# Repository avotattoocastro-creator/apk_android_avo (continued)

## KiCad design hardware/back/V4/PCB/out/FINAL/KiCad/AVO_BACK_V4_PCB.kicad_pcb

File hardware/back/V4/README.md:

# AVO BACK V4 · espalda compacta (PCB propia + URTK1.2 + carcasa más corta)

Rediseño conjunto de la electrónica y la carcasa de la espalda de AVO Performance Horse.
**Estado: DISEÑADO Y COMPROBADO POR SOFTWARE · NO FABRICADO · NO VERIFICADO EN HARDWARE.**

**REV B (30/10/2026): sin Qi ni sensor Hall.** Alimentación por **3 contactos en el fondo** (tornillos M2 avellanados con
junta tórica): **SYS** y **BAT** en la cola, donde estaba el reed, y **GND** aparte.
- **Soporte del chaleco:** 2 pines con muelle unidos por un hilo puentean SYS–BAT. Al poner la cápsula se enciende; al
  quitarla queda a 0 V.
- **Base de carga:** cargador Li-ion externo entre BAT y GND, con la electrónica apagada.
- **USB-C:** se mantiene para el taller (datos y carga).
- **REV A** (con Qi y Hall, puerta superada) congelada en `PCB_REV_A_QI/`.
- **Probarlo antes en la espalda actual** (Rev E + Heltec): `DOCS/PROTOTIPO_POGO_REV_E.md` y `PROTOTIPO_POGO_REV_E6/`.

## Resultado
| Parámetro | Espalda actual (Rev E.5 + Heltec) | Nueva V4 | Diferencia |
|---|---|---|---|
| Longitud de la cápsula | 166,2 mm | **118,2 mm** | **−48,0 mm (−28,9 %)** |
| Anchura | 59,0 mm | 59,0 mm | 0 |
| Grosor de la cápsula | 17,1 mm | **17,1 mm** | **0** (no aumenta) |
| Grosor del conjunto (cápsula + soporte + tela + contraplaca) | 28,2 mm | 28,2 mm | 0 |
| Volumen exterior de la cápsula | 157,8 cm³ | 110,1 cm³ | −47,7 cm³ (−30,3 %) |
| Peso de las piezas impresas (macizas, PETG/TPU) | 208 g | ≈ 131 g | **≈ −77 g (−37 %)** |
| Peso de la electrónica | Heltec + Pololu + módulo Qi + cables | PCB V4 ≈ 9 g (estimado) | similar (sin medir) |
| Autonomía (2000 mAh) | ~8 h (estimada, 190–230 mA) | **≈ 7,8 h** (estimada, ≈ 230 mA) | ≥ 4 h exigidas |
| Consumo fuera del soporte | ZED sin cortar en algunas versiones (~70 mA) | **0 µA** (REV B: sin puente SYS–BAT la placa no tiene alimentación; solo el PCM de la celda) | |
| Placas | 3 (Heltec, URTK1.2, módulo Qi) + regulador Pololu | **2** (PCB V4 + URTK1.2) | −1 (−2 con el Pololu) |
| Cables entre placas | ZED (5–7 hilos), Qi, reed, batería, regulador | **1 mazo de 8 hilos** (URTK1.2 ↔ J4) + batería | |
| Carga | Qi (base inalámbrica) | **contactos BAT–GND** en la base de carga (REV B) · USB-C en el taller | |
| microSD | no | **sí** (SDMMC 4 bits) | |

**PCB REV B:** ruteada al 100 %; KiCad 9 en el CI (run 41048486880, `c1e0e26`; repetida en 41050496945, `6e5b54d`, con las existencias del TVS): DRC 0, ERC 0, 0 conexiones incompletas,
puerta de fabricación superada → `PCB/out/FINAL/` (61 piezas montadas). Su STEP, montado en el CAD a Z 2,5, no interfiere
con ninguna pieza ni con los tornillos de contacto (`CAD/VALIDACION/verificacion_pcb_step_v4.json`).
**PCB REV A** (congelada): puerta superada en el CI (run 40971520610, `3f81b45`) → `PCB_REV_A_QI/out/FINAL/`.

Cotas y volúmenes medidos sobre el modelo B-Rep (no sobre fotos). Pesos: volumen × densidad (PETG 1,27, TPU 1,20 g/cm³),
como en la Rev E.

## Cómo se consigue (sin aumentar el grosor)
- **La URTK1.2 va encima de la batería**, donde estaba la Heltec, a la misma altura (Z 9,6). La L, la torre y la antena
  no cambian de cota.
- **La PCB va en la cola**, el tramo que la antena Q39 obliga a tener por detrás del eje de la L y que en la Rev E
  estaba casi vacío. Bolsillo en la base a Z 2,5 (REV A: bobina Qi debajo; REV B: suelo macizo con los contactos).
- **Un solo ESP32-S3** (no dos): misma funcionalidad, menos consumo y menos superficie (`DOCS/ARQUITECTURA_Y_CONSUMO.md`).
- **Sin sensor de soporte (REV B)**: el propio soporte cierra el circuito (puente SYS–BAT); REV A usaba un Hall soldado.
- **Regulador propio del ZED con EN**: corta físicamente receptor y antena, sin el reinicio de la BACK 3.10.4.

Estudio completo de las alternativas A–D: `DOCS/ESTUDIO_DISTRIBUCION.md`.

## Carpetas
| Carpeta | Contenido |
|---|---|
| `CAD/fuente/` | modelo paramétrico FreeCAD 1.0.2 (`avo_back_v4_freecad.py`), verificación, exportación, voladizos, renders, plano |
| `CAD/STL/` | piezas orientadas para imprimir **sin soportes** + `posicion_montaje/` + probetas |
| `CAD/STEP/` | sólidos B-Rep por pieza, conjunto montado y explosionado |
| `CAD/IMAGENES/`, `CAD/PLANOS/` | vistas, vista explosionada, plano de dimensiones (PDF) y comparativa con la Rev E.5 |
| `CAD/VALIDACION/` | interferencias, STEP/STL, voladizos, informe del modelo |
| `PCB/fuente/` | generador del proyecto KiCad REV B (piezas, redes, colocación), reparación de ruteado, puerta de fabricación |
| `PCB_REV_A_QI/` | placa REV A con Qi y Hall (congelada, puerta superada) |
| `PROTOTIPO_POGO_REV_E6/` | base, soporte y base de carga Rev E.6 para probar los contactos en la espalda actual (Heltec) |
| `PCB/kicad/` | proyecto KiCad 9 editable |
| `PCB/out/` | ERC/DRC, esquema PDF, renders y — si la puerta pasa — `FINAL/` (Gerber, taladros, BOM y CPL de JLCPCB, STEP) |
| `../../../firmware/back/V4_0_0/` | firmware 4.0.0-dev2 de la placa V4 REV B (`../V3_8_0`: BACK 3.12.0 para el prototipo Heltec) |
| `DOCS/` | arquitectura y consumo, integración GNSS, distribución, montaje y riesgos |

## Ejes y origen (CAD, PCB y STEP)
X 0 = cara del cuello, X+ hacia la cola · Y 0 = eje de la L · Z 0 = cara inferior de la cápsula. La PCB de KiCad está en
las mismas coordenadas (x = X, y = 100 − Y; el STEP se exporta con origen de usuario 0 × 100 mm).

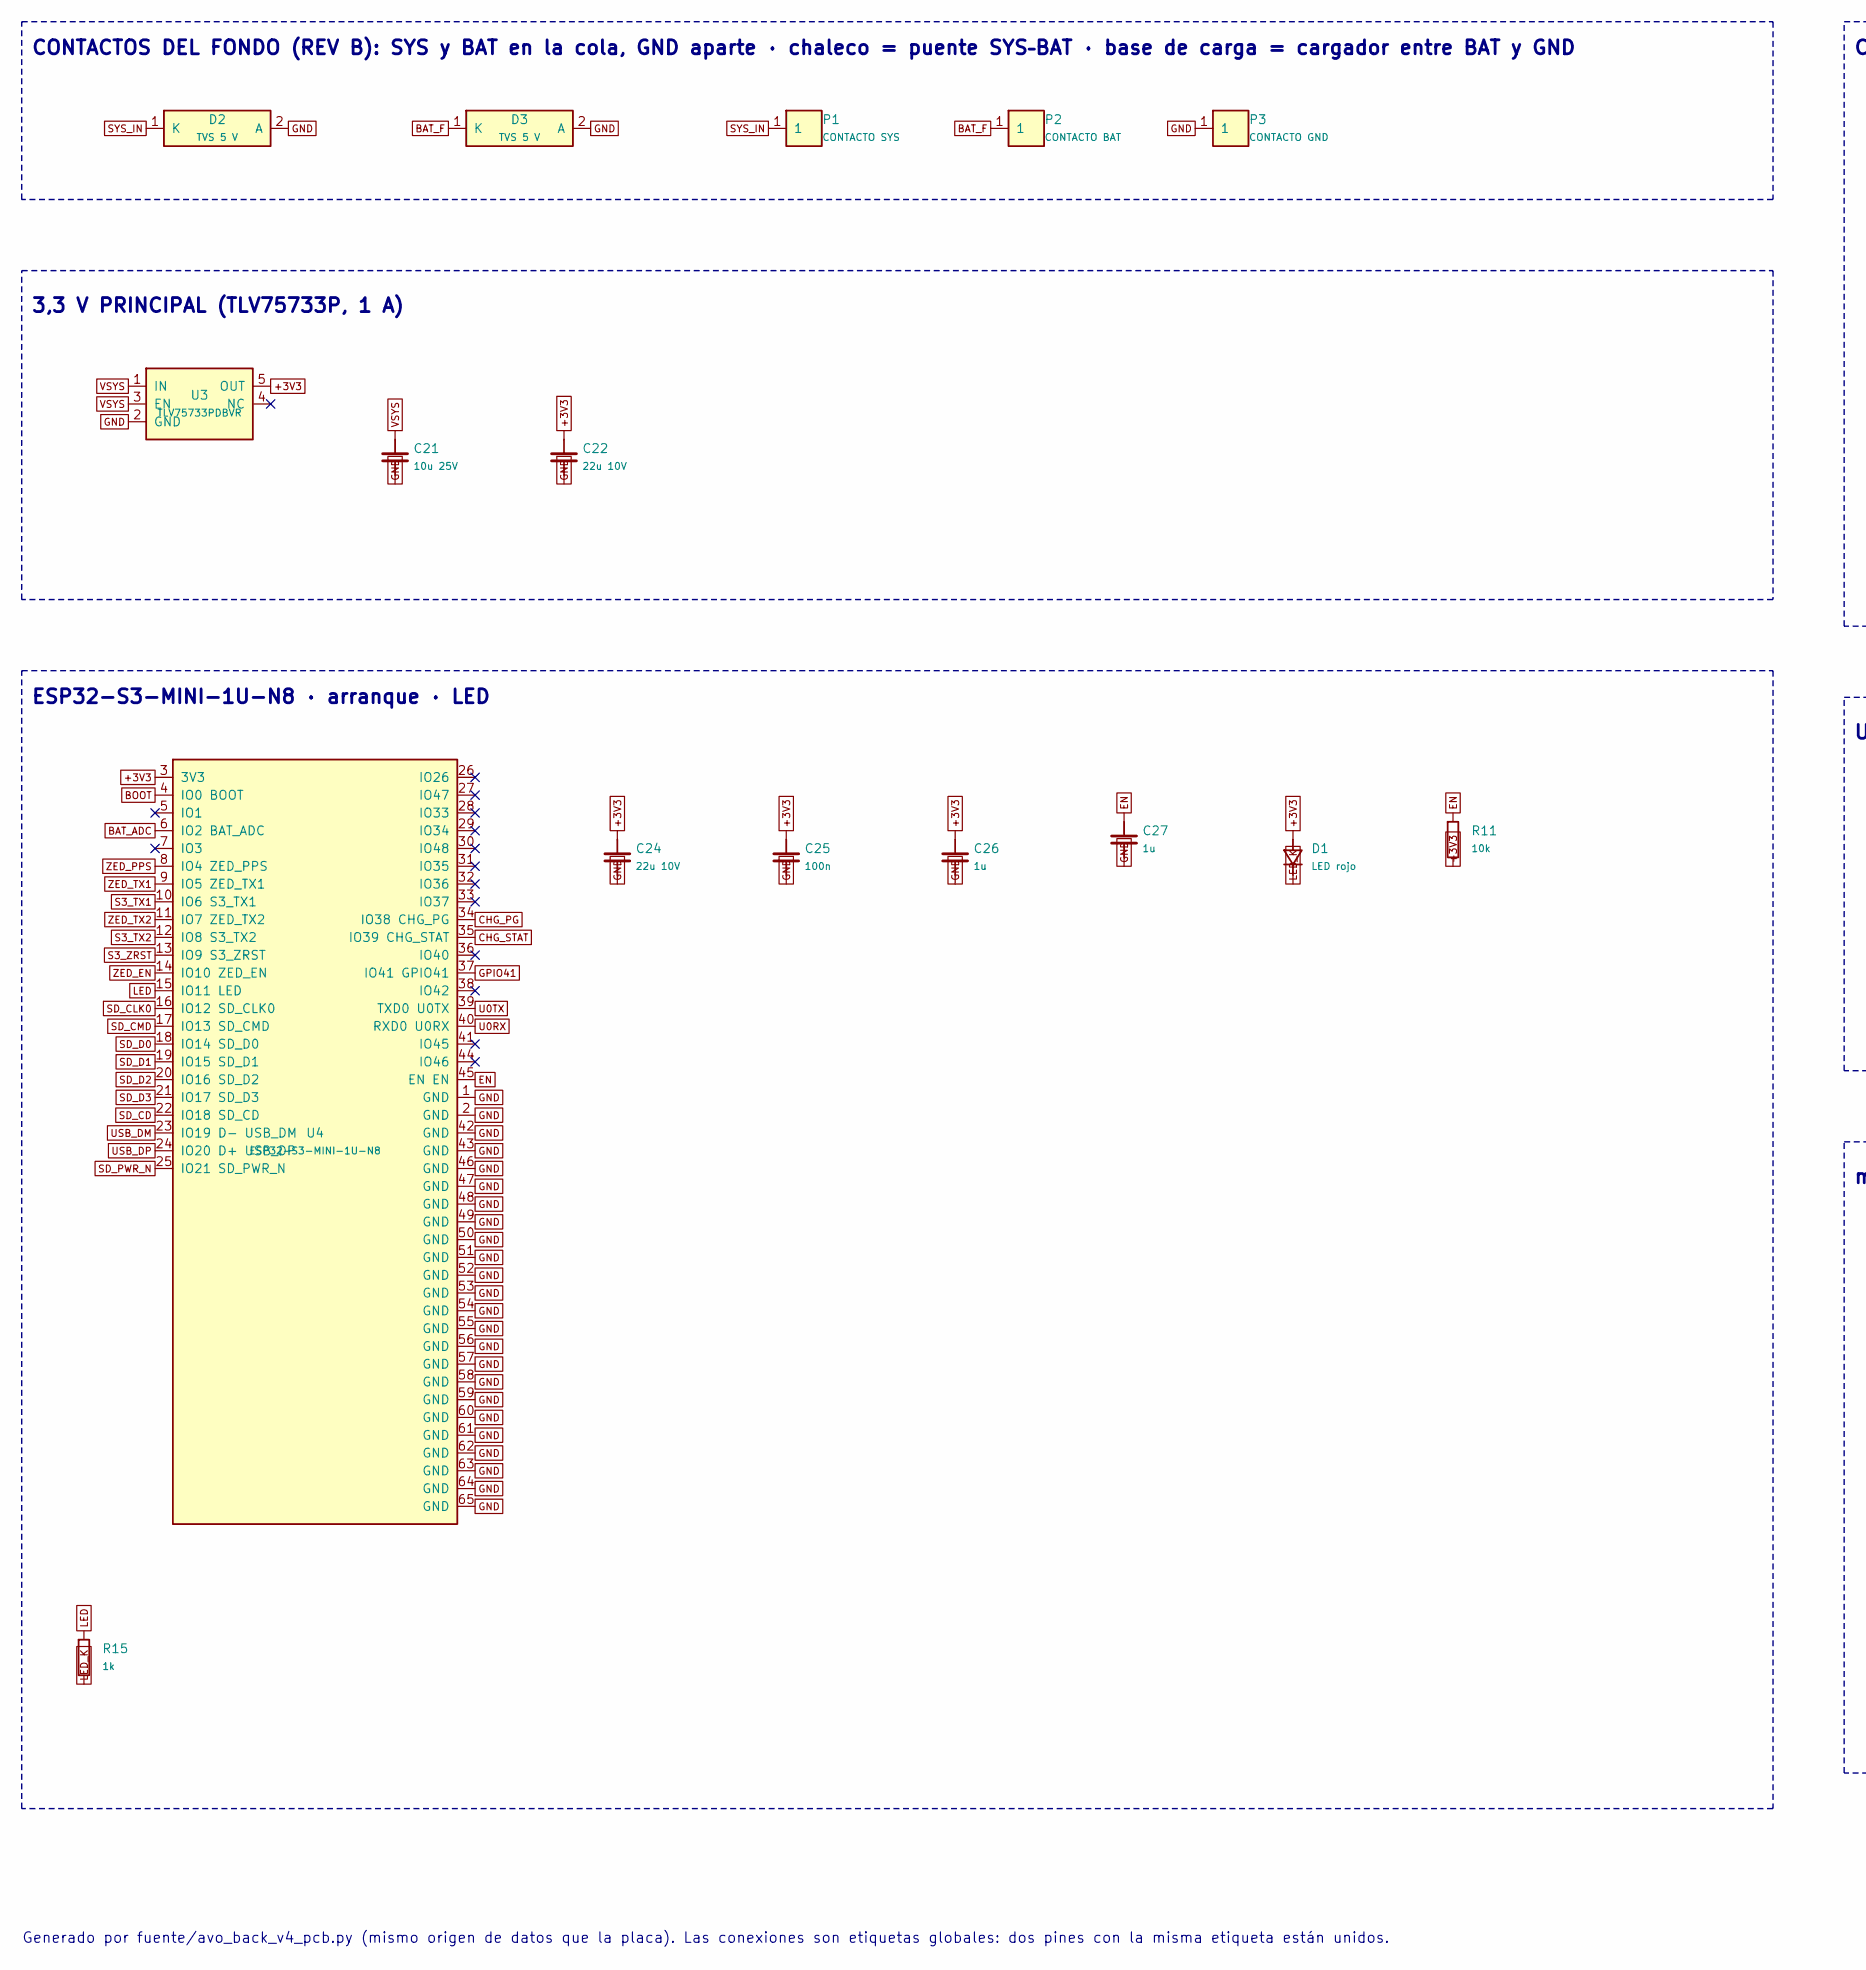
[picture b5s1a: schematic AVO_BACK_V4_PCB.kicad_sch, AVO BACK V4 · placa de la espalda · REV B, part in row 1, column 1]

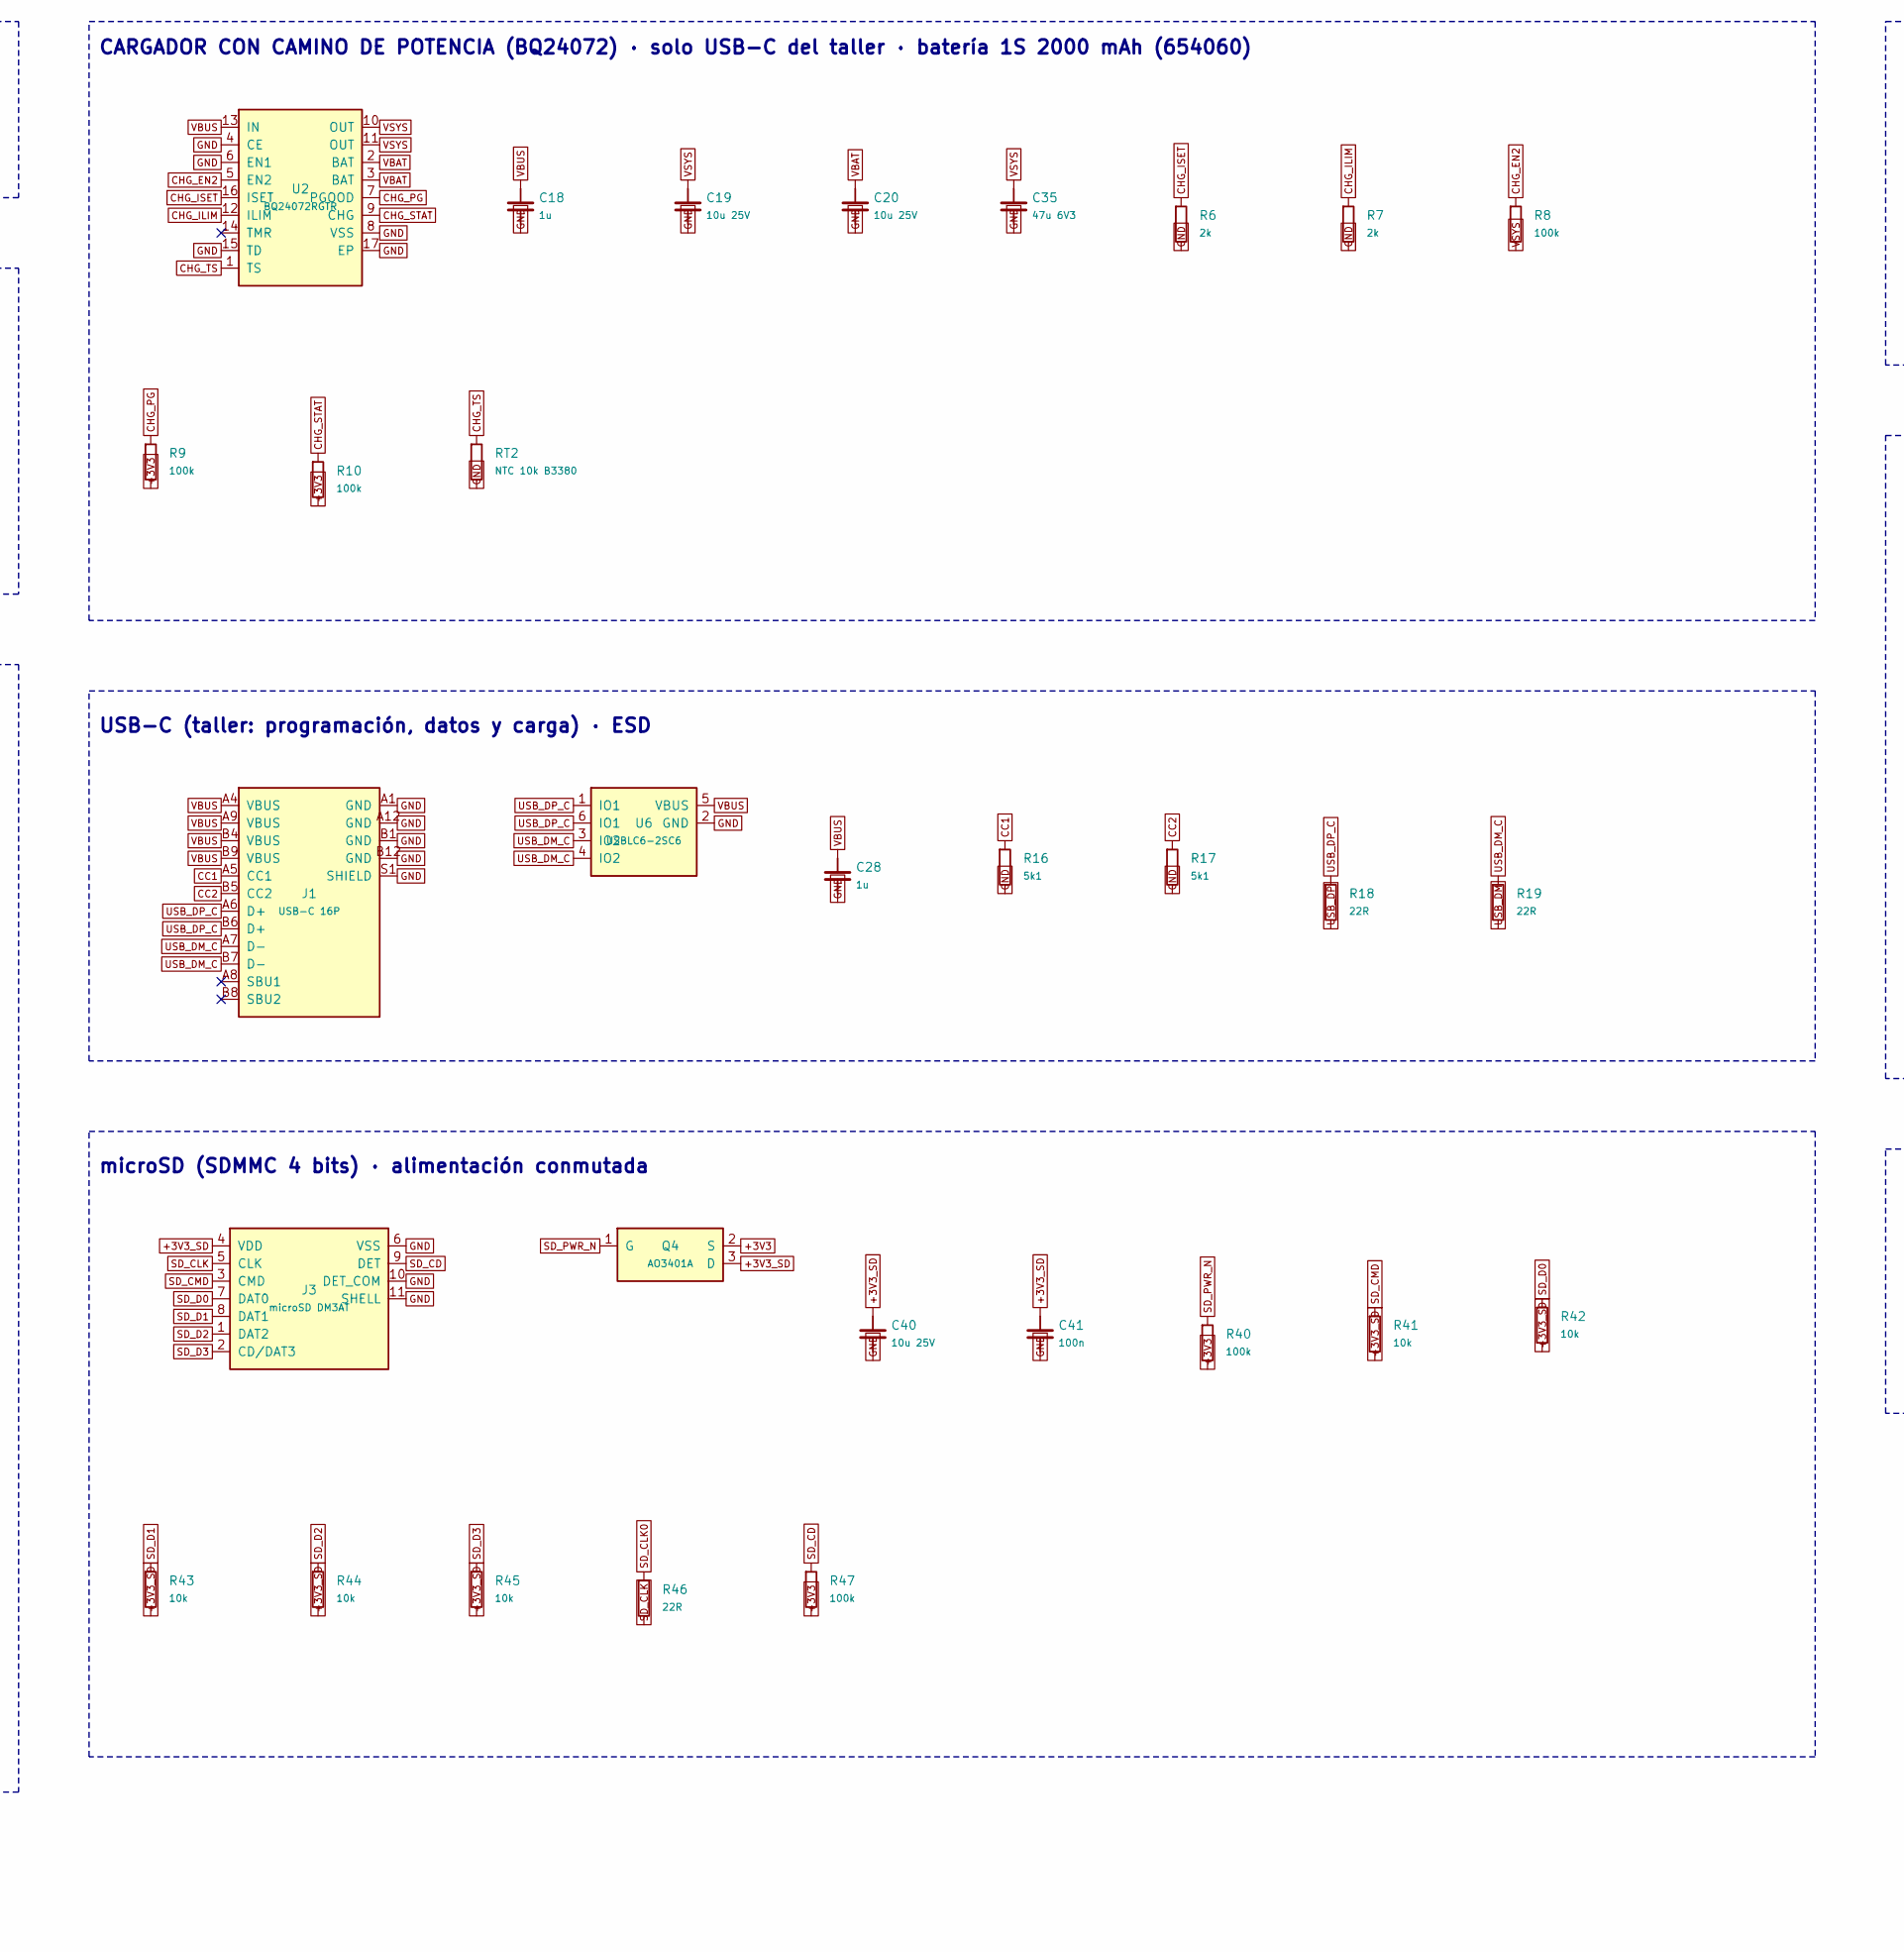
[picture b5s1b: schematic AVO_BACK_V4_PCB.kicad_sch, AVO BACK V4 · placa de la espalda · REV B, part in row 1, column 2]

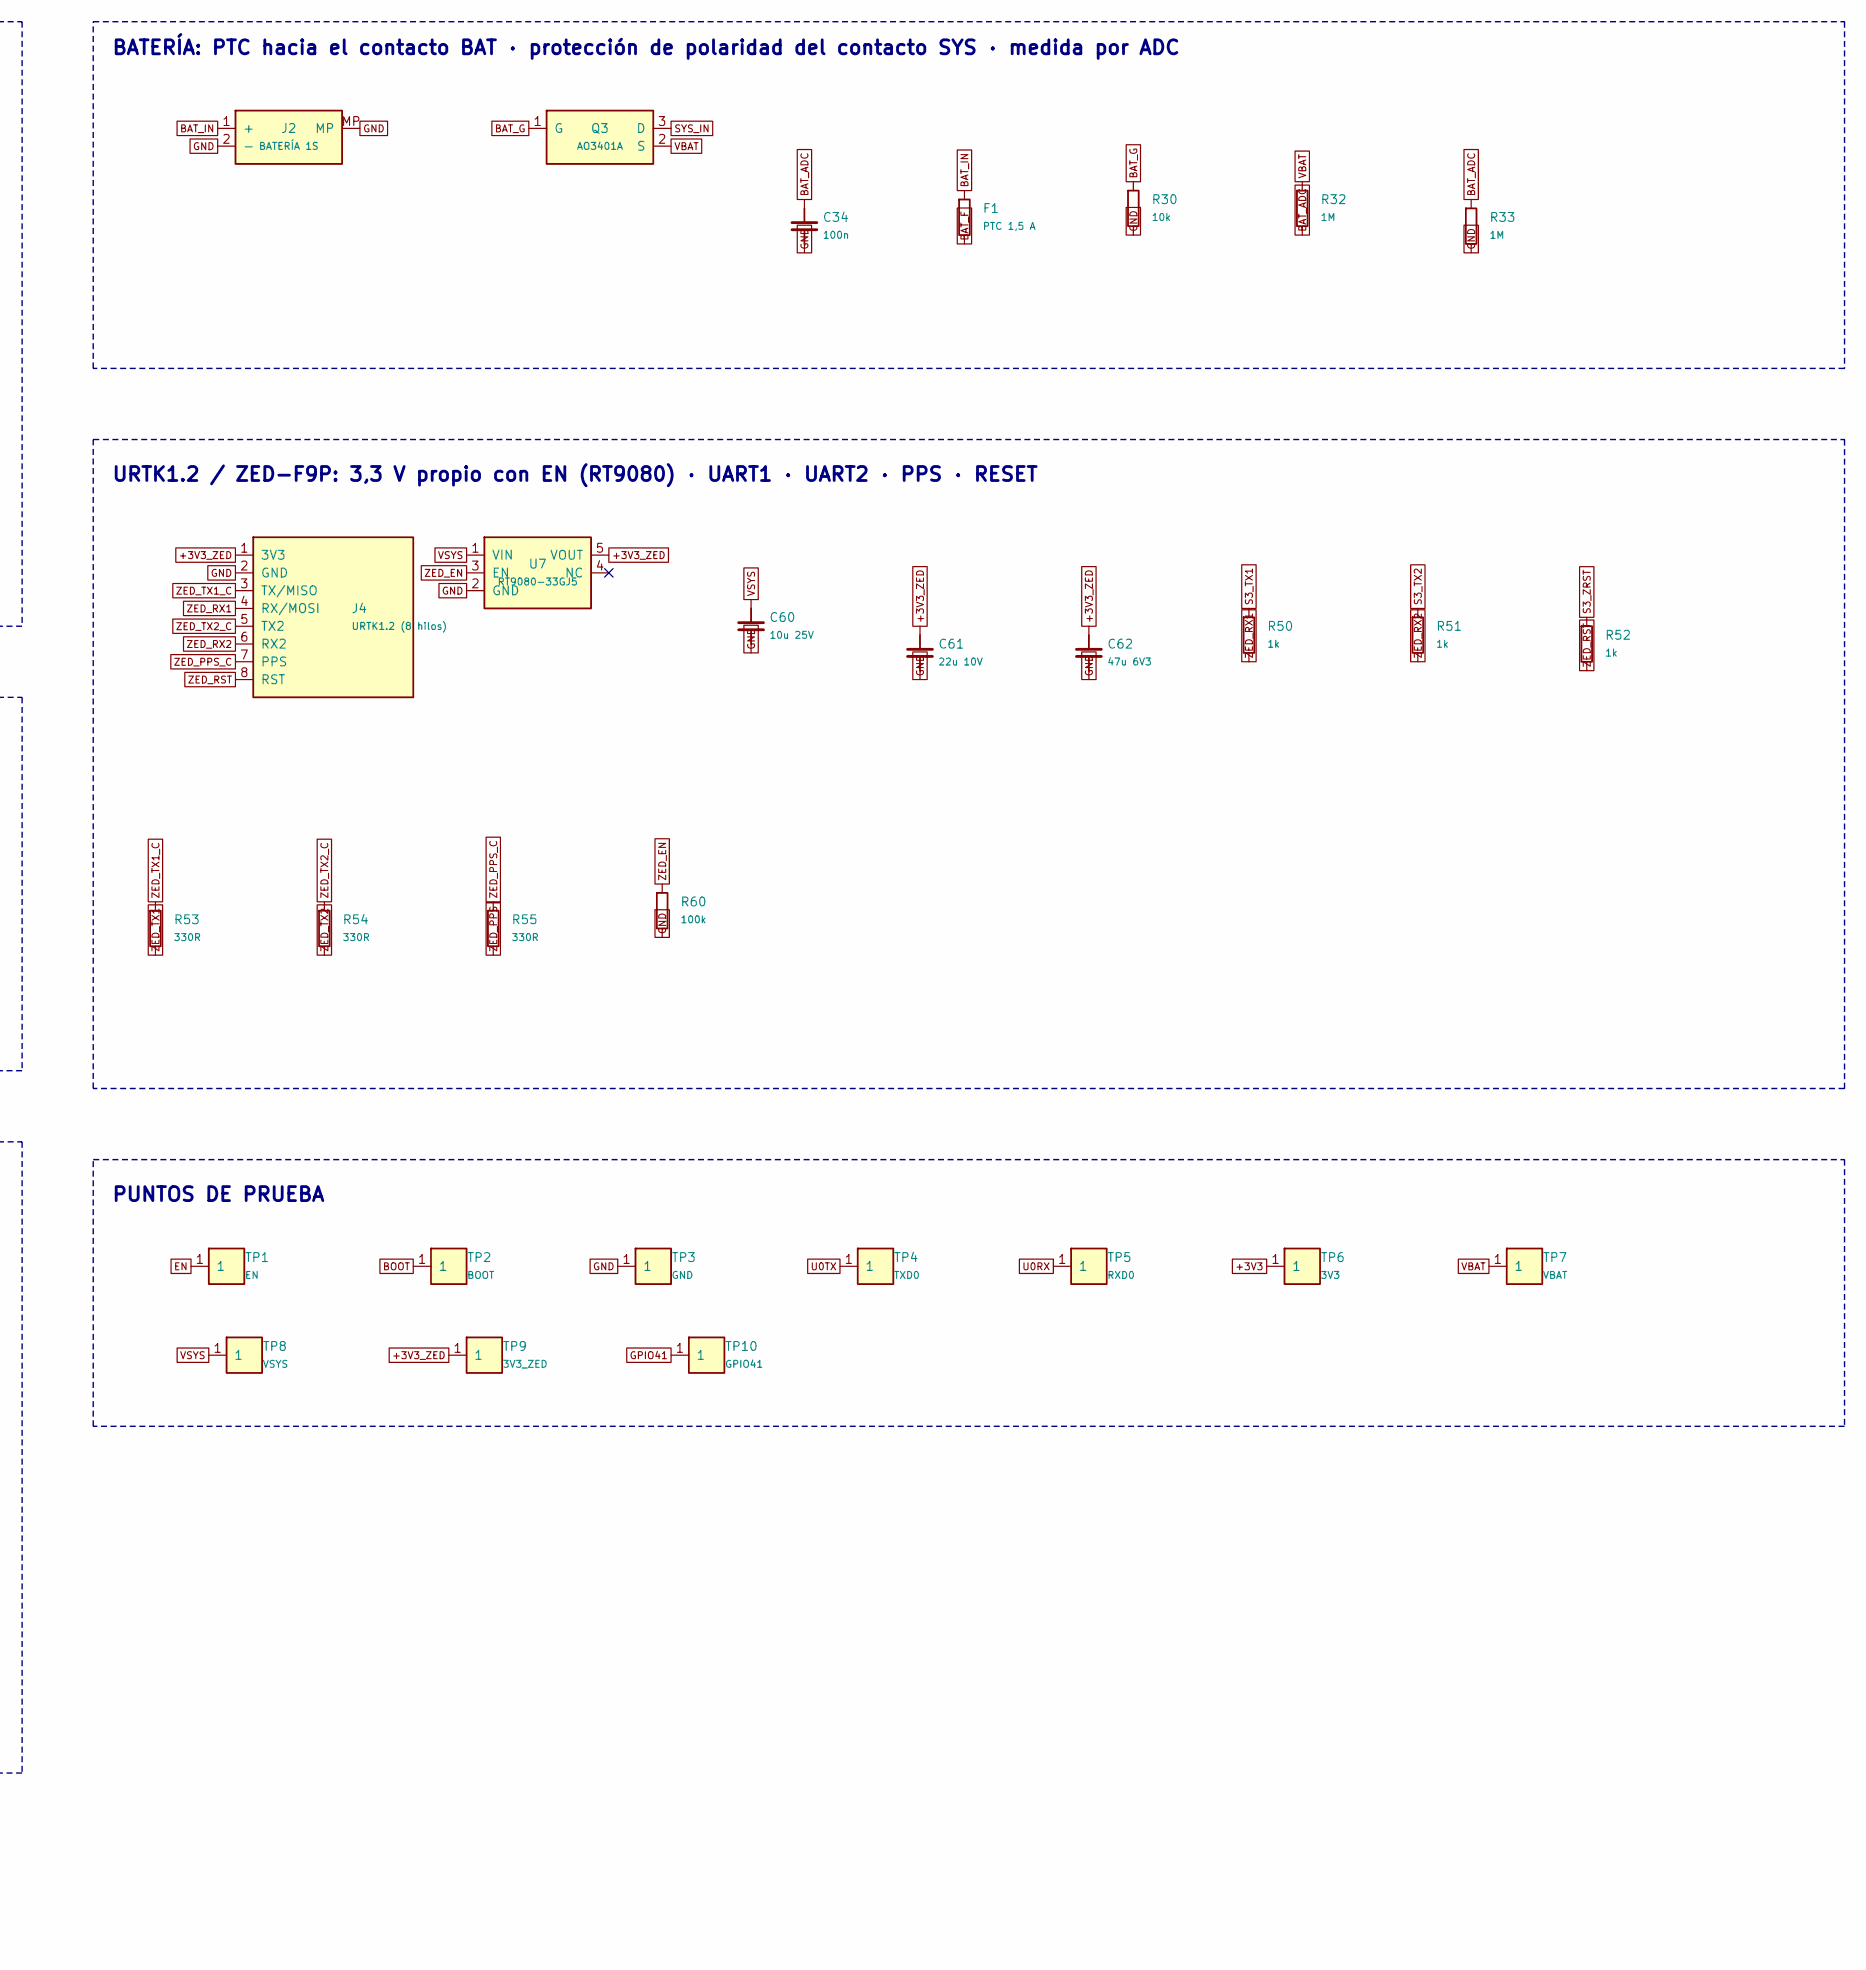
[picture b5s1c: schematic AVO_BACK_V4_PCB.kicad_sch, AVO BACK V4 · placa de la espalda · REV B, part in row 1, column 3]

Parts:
C18, C26, C27, C28: 1u; C_0402_1005Metric; LCSC C52923
C19, C20, C21, C40, C60: 10u 25V; C_0603_1608Metric; LCSC C96446
C22, C24, C61: 22u 10V; C_0805_2012Metric; LCSC C45783
C25, C34, C41: 100n; C_0402_1005Metric; LCSC C1525
C35, C62: 47u 6V3; C_0805_2012Metric; LCSC C16780
D1: LED rojo; LED_0603_1608Metric; MPN KT-0603R; LCSC C2286
D2, D3: TVS 5 V; D_SOD-323; MPN PESD5V0S1BA; LCSC C2827694
F1: PTC 1,5 A; Fuse_1206_3216Metric; MPN SMD1206P150TF; LCSC C20802
J1: USB-C 16P; USB_C_Receptacle_HRO_TYPE-C-31-M-12; MPN TYPE-C-31-M-12; LCSC C165948
J2: BATERÍA 1S; JST_SH_SM02B-SRSS-TB_1x02-1MP_P1.00mm_Horizontal; MPN SM02B-SRSS-TB (JST SH 1,0); LCSC C160402
J3: microSD DM3AT; microSD_HC_Hirose_DM3AT-SF-PEJM5; MPN DM3AT-SF-PEJM5; LCSC C114218
J4: URTK1.2 (8 hilos); AVO_URTK_Pads_2x04_P2.54mm
P1: CONTACTO SYS; AVO_Contacto_M2_Tornillo
P2: CONTACTO BAT; AVO_Contacto_M2_Tornillo
P3: CONTACTO GND; AVO_Contacto_M2_Tornillo
Q3, Q4: AO3401A; SOT-23; LCSC C15127
R6, R7: 2k; R_0402_1005Metric; LCSC C4109
R8, R9, R10, R40, R47, R60: 100k; R_0402_1005Metric; LCSC C25741
R11, R30, R41, R42, R43, R44, R45: 10k; R_0402_1005Metric; LCSC C25744
R15, R50, R51, R52: 1k; R_0402_1005Metric; LCSC C11702
R16, R17: 5k1; R_0402_1005Metric; LCSC C25905
R18, R19, R46: 22R; R_0402_1005Metric; LCSC C25092
R32, R33: 1M; R_0402_1005Metric; LCSC C26083
R53, R54, R55: 330R; R_0402_1005Metric; LCSC C25104
RT2: NTC 10k B3380; R_0402_1005Metric; MPN NCP15XH103F03RC; LCSC C77131
TP1: EN; TestPoint_Pad_D1.0mm
TP2: BOOT; TestPoint_Pad_D1.0mm
TP3: GND; TestPoint_Pad_D1.0mm
TP4: TXD0; TestPoint_Pad_D1.0mm
TP5: RXD0; TestPoint_Pad_D1.0mm
TP6: 3V3; TestPoint_Pad_D1.0mm
TP7: VBAT; TestPoint_Pad_D1.0mm
TP8: VSYS; TestPoint_Pad_D1.0mm
TP9: 3V3_ZED; TestPoint_Pad_D1.0mm
TP10: GPIO41; TestPoint_Pad_D1.0mm
U2: BQ24072RGTR; VQFN-16-1EP_3x3mm_P0.5mm_EP1.68x1.68mm_ThermalVias; MPN BQ24072RGTR; LCSC C140288
U3: TLV75733PDBVR; SOT-23-5; MPN TLV75733PDBVR; LCSC C485517
U4: ESP32-S3-MINI-1U-N8; ESP32-S3-MINI-1U; MPN ESP32-S3-MINI-1U-N8; LCSC C2980299
U6: USBLC6-2SC6; SOT-23-6; LCSC C7519
U7: RT9080-33GJ5; SOT-23-5; MPN RT9080-33GJ5; LCSC C841192

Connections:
+3V3: C22.1, C24.1, C25.1, C26.1, D1.2 (A), Q4.2 (S), R9.2, R10.2, R11.2, R40.2, R47.2, TP6.1, U3.5 (OUT), U4.3 (3V3)
+3V3_SD: C40.1, C41.1, J3.4 (VDD), Q4.3 (D), R41.2, R42.2, R43.2, R44.2, R45.2
+3V3_ZED: C61.1, C62.1, J4.1 (3V3), TP9.1, U7.5 (VOUT)
BAT_ADC: C34.1, R32.2, R33.1, U4.6 (IO2 BAT_ADC)
BAT_F: D3.1 (K), F1.2, P2.1
BAT_G: Q3.1 (G), R30.1
BAT_IN: F1.1, J2.1 (+)
BOOT: TP2.1, U4.4 (IO0 BOOT)
CC1: J1.A5 (CC1), R16.1
CC2: J1.B5 (CC2), R17.1
CHG_EN2: R8.1, U2.5 (EN2)
CHG_ILIM: R7.1, U2.12 (ILIM)
CHG_ISET: R6.1, U2.16 (ISET)
CHG_PG: R9.1, U2.7 (PGOOD), U4.34 (IO38 CHG_PG)
CHG_STAT: R10.1, U2.9 (CHG), U4.35 (IO39 CHG_STAT)
CHG_TS: RT2.1, U2.1 (TS)
EN: C27.1, R11.1, TP1.1, U4.45 (EN EN)
GND: C18.2, C19.2, C20.2, C21.2, C22.2, C24.2, C25.2, C26.2, C27.2, C28.2, C34.2, C35.2, C40.2, C41.2, C60.2, C61.2, C62.2, D2.2 (A), D3.2 (A), J1.A1 (GND), J1.A12 (GND), J1.B1 (GND), J1.B12 (GND), J1.S1 (SHIELD), J2.2 (−), J2.MP, J3.6 (VSS), J3.10 (DET_COM), J3.11 (SHELL), J4.2 (GND), P3.1, R6.2, R7.2, R16.2, R17.2, R30.2, R33.2, R60.2, RT2.2, TP3.1, U2.4 (CE), U2.6 (EN1), U2.8 (VSS), U2.15 (TD), U2.17 (EP), U3.2 (GND), U4.1 (GND), U4.2 (GND), U4.42 (GND), U4.43 (GND), U4.46 (GND), U4.47 (GND), U4.48 (GND), U4.49 (GND), U4.50 (GND), U4.51 (GND), U4.52 (GND), U4.53 (GND), U4.54 (GND), U4.55 (GND), U4.56 (GND), U4.57 (GND), U4.58 (GND), U4.59 (GND), U4.60 (GND), U4.61 (GND), U4.62 (GND), U4.63 (GND), U4.64 (GND), U4.65 (GND), U6.2 (GND), U7.2 (GND)
GPIO41: TP10.1, U4.37 (IO41 GPIO41)
LED: R15.1, U4.15 (IO11 LED)
LED_K: D1.1 (K), R15.2
S3_TX1: R50.1, U4.10 (IO6 S3_TX1)
S3_TX2: R51.1, U4.12 (IO8 S3_TX2)
S3_ZRST: R52.1, U4.13 (IO9 S3_ZRST)
SD_CD: J3.9 (DET), R47.1, U4.22 (IO18 SD_CD)
SD_CLK: J3.5 (CLK), R46.2
SD_CLK0: R46.1, U4.16 (IO12 SD_CLK0)
SD_CMD: J3.3 (CMD), R41.1, U4.17 (IO13 SD_CMD)
SD_D0: J3.7 (DAT0), R42.1, U4.18 (IO14 SD_D0)
SD_D1: J3.8 (DAT1), R43.1, U4.19 (IO15 SD_D1)
SD_D2: J3.1 (DAT2), R44.1, U4.20 (IO16 SD_D2)
SD_D3: J3.2 (CD/DAT3), R45.1, U4.21 (IO17 SD_D3)
SD_PWR_N: Q4.1 (G), R40.1, U4.25 (IO21 SD_PWR_N)
SYS_IN: D2.1 (K), P1.1, Q3.3 (D)
U0RX: TP5.1, U4.40 (RXD0 U0RX)
U0TX: TP4.1, U4.39 (TXD0 U0TX)
USB_DM: R19.2, U4.23 (IO19 D- USB_DM)
USB_DM_C: J1.A7 (D−), J1.B7 (D−), R19.1, U6.3 (IO2), U6.4 (IO2)
USB_DP: R18.2, U4.24 (IO20 D+ USB_DP)
USB_DP_C: J1.A6 (D+), J1.B6 (D+), R18.1, U6.1 (IO1), U6.6 (IO1)
VBAT: C20.1, Q3.2 (S), R32.1, TP7.1, U2.2 (BAT), U2.3 (BAT)
VBUS: C18.1, C28.1, J1.A4 (VBUS), J1.A9 (VBUS), J1.B4 (VBUS), J1.B9 (VBUS), U2.13 (IN), U6.5 (VBUS)
VSYS: C19.1, C21.1, C35.1, C60.1, R8.2, TP8.1, U2.10 (OUT), U2.11 (OUT), U3.1 (IN), U3.3 (EN), U7.1 (VIN)
ZED_EN: R60.1, U4.14 (IO10 ZED_EN), U7.3 (EN)
ZED_PPS: R55.2, U4.8 (IO4 ZED_PPS)
ZED_PPS_C: J4.7 (PPS), R55.1
ZED_RST: J4.8 (RST), R52.2
ZED_RX1: J4.4 (RX/MOSI), R50.2
ZED_RX2: J4.6 (RX2), R51.2
ZED_TX1: R53.2, U4.9 (IO5 ZED_TX1)
ZED_TX1_C: J4.3 (TX/MISO), R53.1
ZED_TX2: R54.2, U4.11 (IO7 ZED_TX2)
ZED_TX2_C: J4.5 (TX2), R54.1

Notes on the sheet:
CONTACTOS DEL FONDO (REV B): SYS y BAT en la cola, GND aparte · chaleco = puente SYS–BAT · base de carga = cargador entre BAT y GND
USB-C (taller: programación, datos y carga) · ESD
BATERÍA: PTC hacia el contacto BAT · protección de polaridad del contacto SYS · medida por ADC
microSD (SDMMC 4 bits) · alimentación conmutada
URTK1.2 / ZED-F9P: 3,3 V propio con EN (RT9080) · UART1 · UART2 · PPS · RESET
CARGADOR CON CAMINO DE POTENCIA (BQ24072) · solo USB-C del taller · batería 1S 2000 mAh (654060)
3,3 V PRINCIPAL (TLV75733P, 1 A)
ESP32-S3-MINI-1U-N8 · arranque · LED
PUNTOS DE PRUEBA
Generado por fuente/avo_back_v4_pcb.py (mismo origen de datos que la placa). Las conexiones son etiquetas globales: dos pines con la misma etiqueta están unidos.

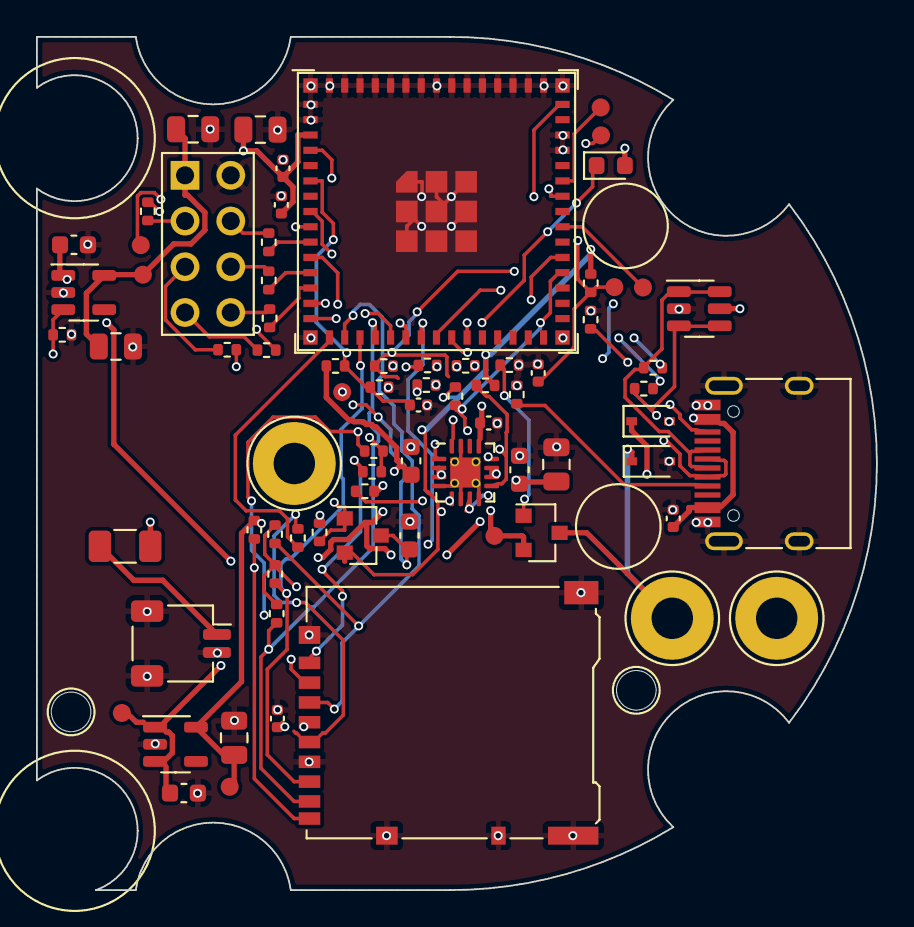
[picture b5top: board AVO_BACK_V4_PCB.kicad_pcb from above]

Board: 4 copper layers, 46.7 x 47.4 mm, 81 parts (0 on the bottom side), 53 nets.

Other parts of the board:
H1, H2: PIVOTE; AVO_Pivote_NPTH_D2.2
MP1, MP2: PISADOR; AVO_Zona_Libre_R2.5
MR1, MR2: ANILLO; AVO_Zona_Libre_R4.6

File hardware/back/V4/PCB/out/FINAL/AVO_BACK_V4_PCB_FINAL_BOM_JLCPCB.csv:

Comment,Designator,Footprint,LCSC Part #
BQ24072RGTR,U2,VQFN-16-1EP_3x3mm_P0.5mm_EP1.68x1.68mm_ThermalVias,C140288
1u,"C18,C26,C27,C28",C_0402_1005Metric,C52923
10u 25V,"C19,C20,C21,C40,C60",C_0603_1608Metric,C96446
47u 6V3,"C35,C62",C_0805_2012Metric,C16780
2k,"R6,R7",R_0402_1005Metric,C4109
NTC 10k B3380,RT2,R_0402_1005Metric,C77131
100k,"R8,R9,R10,R40,R47,R60",R_0402_1005Metric,C25741
BATERÍA 1S,J2,JST_SH_SM02B-SRSS-TB_1x02-1MP_P1.00mm_Horizontal,C160402
"PTC 1,5 A",F1,Fuse_1206_3216Metric,C20802
AO3401A,"Q3,Q4",SOT-23,C15127
TVS 5 V,"D2,D3",D_SOD-323,C2827694
10k,"R11,R30,R41,R42,R43,R44,R45",R_0402_1005Metric,C25744
1M,"R32,R33",R_0402_1005Metric,C26083
100n,"C25,C34,C41",C_0402_1005Metric,C1525
TLV75733PDBVR,U3,SOT-23-5,C485517
22u 10V,"C22,C24,C61",C_0805_2012Metric,C45783
RT9080-33GJ5,U7,SOT-23-5,C841192
ESP32-S3-MINI-1U-N8,U4,ESP32-S3-MINI-1U,C2980299
1k,"R15,R50,R51,R52",R_0402_1005Metric,C11702
LED rojo,D1,LED_0603_1608Metric,C2286
USB-C 16P,J1,USB_C_Receptacle_HRO_TYPE-C-31-M-12,C165948
5k1,"R16,R17",R_0402_1005Metric,C25905
USBLC6-2SC6,U6,SOT-23-6,C7519
22R,"R18,R19,R46",R_0402_1005Metric,C25092
microSD DM3AT,J3,microSD_HC_Hirose_DM3AT-SF-PEJM5,C114218
330R,"R53,R54,R55",R_0402_1005Metric,C25104
